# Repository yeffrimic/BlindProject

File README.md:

# Blind project

Is an open project that want to give blind people a new way to feel the world, using an ultrasonic sensor to measure the distance between the device and an obstacle a meter away.
[website](https://yeffrimic.github.io/proyectos/sonar.html)
## Usage
you can use it as a clothespin, just need to put in the clothes.

## Team Members
[Yeffri J. Salazar](https://yeffrimic.github.io) team leader, prototyping.<br>
[Sebastian Juarez](https://jucamake.wordpress.com) 3d design.<br>
[Elmer Colchaj](https://www.facebook.com/E.R.C.G.X) schematic and PCB design.<br>

## Requirements
* [Attiny85.](http://www.ebay.com/itm/10PCS-ATTINY13A-PU-ATTINY13A-DIP8-IC-MCU-AVR-1K-FLASH-20MHZ-ATMEL-NEW-/191674226371)
* [two transistors 2n3904.](http://www.ebay.com/itm/100Pcs-2N3904-TO-92-NPN-General-Purpose-Transistor-/381374819086?hash=item58cbb5eb0e:g:UwoAAOxyyFhTeDDy)
* [push button two pins.](http://www.ebay.com/itm/100pcs-2pins-Tactile-Push-Button-Switch-Tact-Switch-6X6X5mm-Momentary-/291613157808?hash=item43e57fa9b0:g:LG4AAOSwQaJXRdV2)
* [socket 8 pins.](http://www.ebay.com/itm/10PCS-8-Pins-DIP-IC-Sockets-Adaptor-Solder-Type-Socket-/161009224443?hash=item257ce5cafb:g:xaQAAOxyhodRzwOe)
* [USB cable.](http://www.ebay.com/itm/10Pcs-USB2-0-Type-A-Plug-4-pin-Male-Adapter-Connector-jack-Black-Plastic-Cover-/272041592227?hash=item3f56f145a3:g:auQAAOSwiYFXHd-g)
* [ultrasonic sensor HC-SR04.](http://www.ebay.com/itm/5pcs-Ultrasonic-Module-HC-SR04-Distance-Measuring-Transducer-Sensor-for-Arduino-/381374789471?hash=item58cbb5775f:g:Rd0AAOxySoJTWL-h)
* [coin vibrator.](http://www.ebay.com/itm/3V-DC-Coin-Sized-Vibration-Motor-10mm-x-3-3mm-x2-Atmel-AVR-Arduino-/131671891439?hash=item1ea8419def:g:liMAAOSwHQ9WUpaR)

## Installation
Download the sketch and upload the code to an ATtiny 85<br />
tutorial: https://themicrofcontrol.wordpress.com/2016/06/03/como-programar-un-attiny-con-arduino/
Please change the LED2 by the coin vibrator.
##Circuit

##Board
 the board was made in proteus by labcenter the file is in the proteus folder

##Issues

## STL FILES
The files are in the 3d files folder.
[Front] (https://github.com/yeffrimic/BlindProject/blob/master/3d%20files/Pieza1.STL)
[Back] (https://github.com/yeffrimic/BlindProject/blob/master/3d%20files/Pieza2.STL)

## Mounting case
#####Images

### Sonar is part of [AGHA Asociacion Guatemalteca de Hardware Abierto <br> ](https://www.facebook.com/hardwaregt)
### Sonar is part of [Comunidad Arduino Guatemala <br> ](https://www.facebook.com/ArduinoGuatemala)
## Sponsored by [TETTSA ](https://www.facebook.com/Electronica-Tettsa-336404033108589/?fref=ts)
<br /><span xmlns:dct="http://purl.org/dc/terms/" property="dct:title">Blind project</span> por <a xmlns:cc="http://creativecommons.org/ns#" href="https://github.com/yeffrimic/BlindProject" property="cc:attributionName" rel="cc:attributionURL">Yeffri salazar</a> se distribuye bajo una <a rel="license" href="http://creativecommons.org/licenses/by-sa/4.0/">Licencia Creative Commons Atribución-CompartirIgual 4.0 Internacional</a>.<br />Basada en una obra en <a xmlns:dct="http://purl.org/dc/terms/" href="https://github.com/yeffrimic/BlindProject/blob/master/blindProject/blindProject.ino" rel="dct:source">https://github.com/yeffrimic/BlindProject/blob/master/blindProject/blindProject.ino</a>.

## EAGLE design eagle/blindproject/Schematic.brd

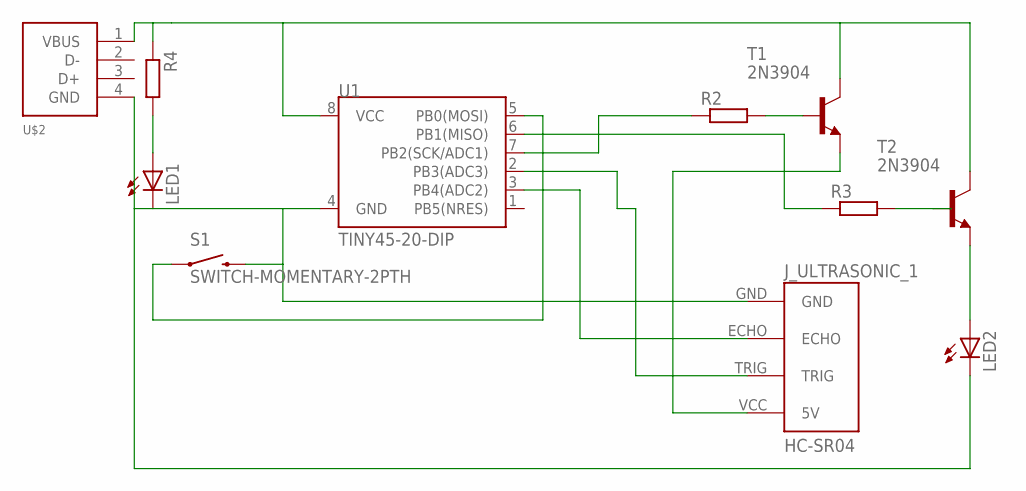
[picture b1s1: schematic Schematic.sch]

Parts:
J_ULTRASONIC_1: HC-SR04; HC-SR04_FOOTPRINT
LED1, LED2: LED_ELD260; LED_LD260
R2, R3, R4: RR1206; R1206
S1: SWITCH-MOMENTARY-2PTH; TACTILE-PTH
T1, T2: 2N3904; TO92
U1: TINY45-20-DIP; DIP08
U$2: USB-CON-4PIN; USB-MALE-A-PCB

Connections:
unnamed: R2.1, U1.7 (PB2(SCK/ADC1))
unnamed: R3.1, U1.6 (PB1(MISO))
unnamed: LED2.A, T2.3 (E)
unnamed: R4.1, T1.1 (C), T2.1 (C), U1.8 (VCC), U$2.1 (VBUS)
unnamed: R2.2, T1.2 (B)
unnamed: R3.2, T2.2 (B)
unnamed: J_ULTRASONIC_1.GND, LED1.K (C), LED2.K (C), S1.3 (2), U1.4 (GND), U$2.4 (GND)
unnamed: J_ULTRASONIC_1.ECHO, U1.3 (PB4(ADC2))
unnamed: J_ULTRASONIC_1.TRIG, U1.2 (PB3(ADC3))
unnamed: J_ULTRASONIC_1.VCC (5V), T1.3 (E)
unnamed: S1.1, U1.5 (PB0(MOSI))
unnamed: LED1.A, R4.2

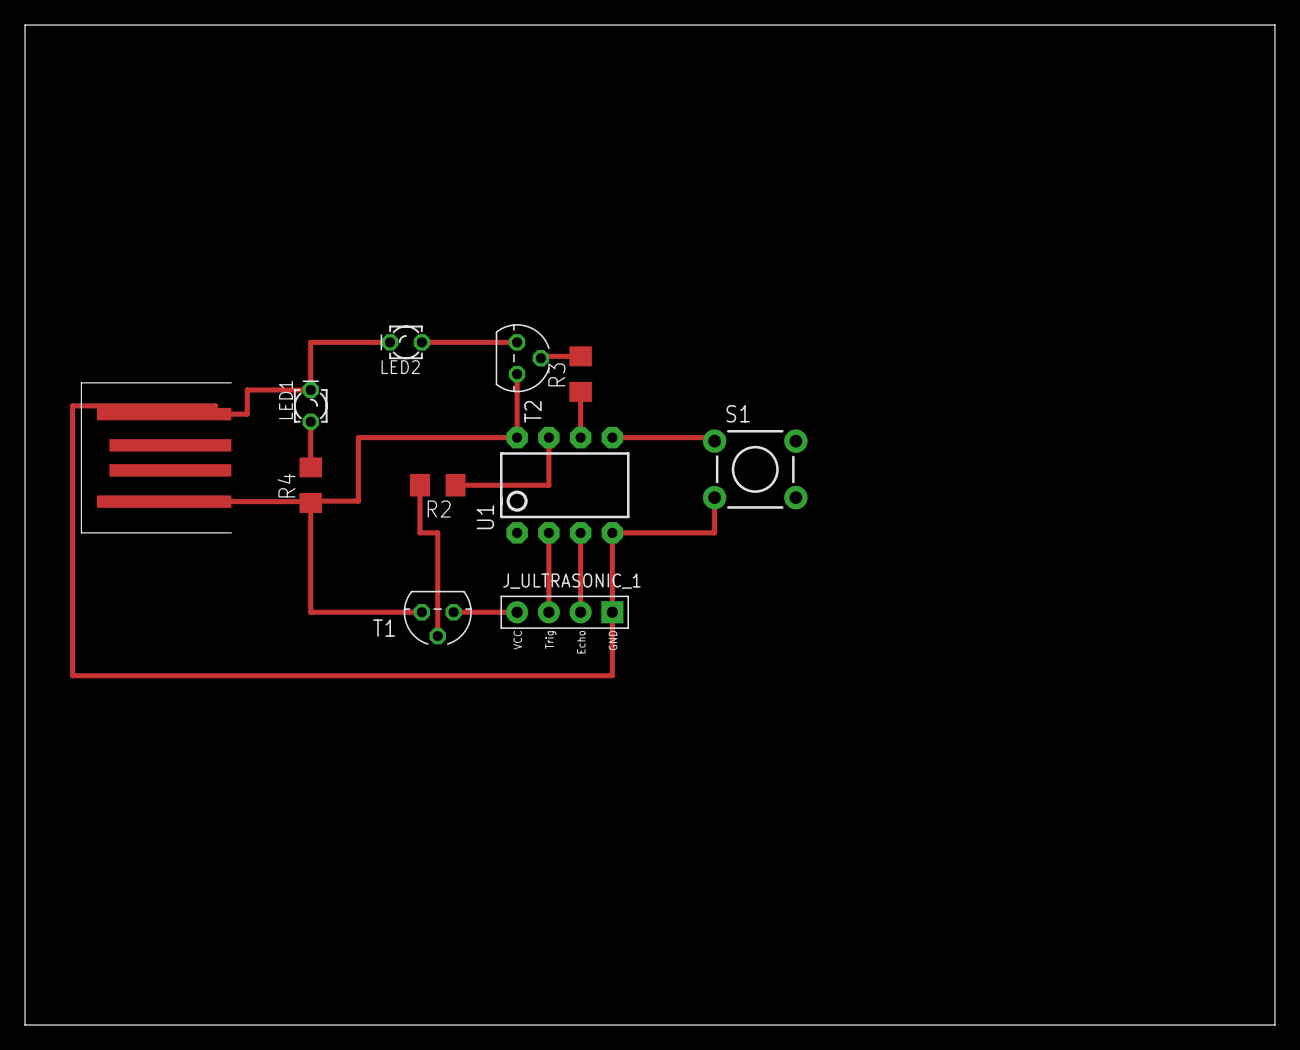
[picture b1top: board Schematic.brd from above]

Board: 2 copper layers, 100.0 x 80.0 mm, 11 parts (0 on the bottom side), 12 nets.

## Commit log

2016-05-31 second commit, first code try
2016-05-31 first try 1 mt max
2016-05-31 adding an int variable to store the data and compare it to
2016-05-31 adding comments and license
2016-06-06 new pins 3 echo ,4 trigger, 1 motor.
2016-06-14 update.
2016-06-20 update code, new variables, button added, faster
2016-07-05 add images
2016-07-10 adding 3d files
2016-07-10 adding photos
2016-07-10 Update README.md
    :)
2016-07-11 Fix style and typos
2016-07-14 change button and vcc sensor pins
2016-07-14 adding eagle files
2016-07-14 adding image eagle files
2016-08-06 adding image and layout pcb files
2016-08-23 adding images update readme
2016-08-30 adding image agha and arduinogt

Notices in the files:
parts and their libraries:
GeekAmmo: Licensing:Creative Commons ShareAlike 4.0 International - https://creativecommons.org/licenses/by-sa/4.0
